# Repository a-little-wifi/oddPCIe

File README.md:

# oddPCIe
PCIe + M.2 SATA breakout for Dell Latitude laptop optical drive modular bay

The optical drive (odd) SATA ports on a number of Dell Latitude laptops from 2011-2013 have a PCIe x1 lane hidden in them, meant for use with the AE3USB01 (DP/N P5MKF) USB 3.0 expansion module:  

> 

> Optical bay port in an E6420, note the second row of pins

## Laptops featuring this port:
* E6320
* E6330 / E6430s
* E6420
* E6430
* E6440
* E6520
* E6530
* E6540 / M2800

Note: The E6440, E6540 and M2800 don't seem to support hot-plug on this PCIe port, as they never actually shipped with anything using this port (the AE3USB01's bezel doesn't even line up with the case)  

## Features:

* PCIe x1 on a USB 3.0 type-a plug compatible with common mining risers
* M.2 SATA SSD slot, since the SATA port is there anyway
* Testpoints for misc pins on the connector

> 
> 

> oddPCIe plugged in to 2 different laptops, showing the fit

> 

> 3.3V regulator power led lighting up

**This board has been manufactured and tested working**  
PCIe port only active if CLKREQ pad is connected to ground  
SATA power only active if PRES pad is connected to ground

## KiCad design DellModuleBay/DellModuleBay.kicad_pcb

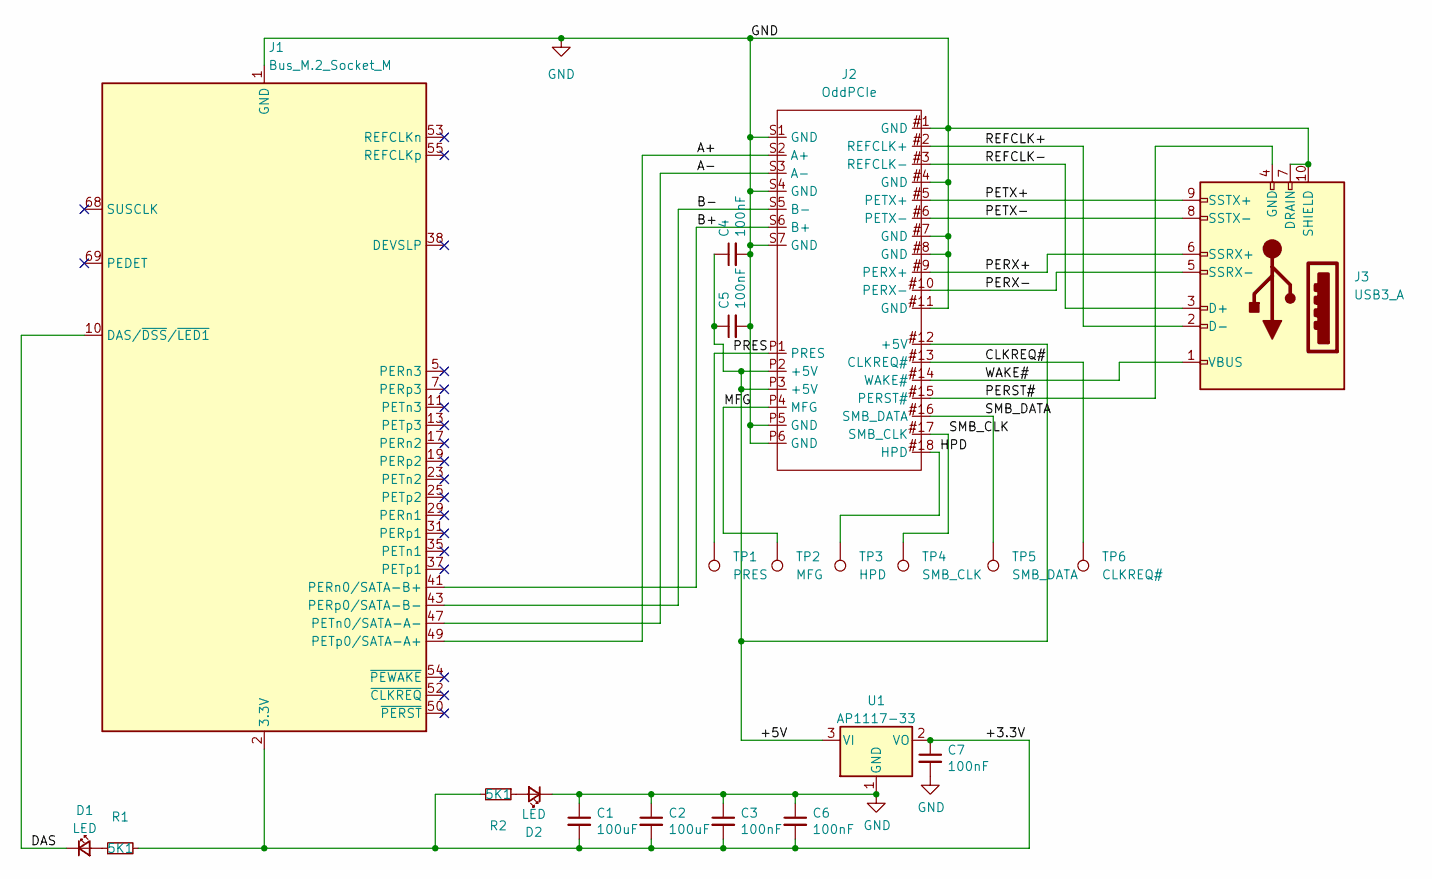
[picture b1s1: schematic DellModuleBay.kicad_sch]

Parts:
C1, C2: 100uF; C_0805_2012Metric
C3, C4, C5, C6, C7: 100nF; C_0805_2012Metric
D1, D2: LED; D_0805_2012Metric
J1: Bus_M.2_Socket_M; m-key
J2: OddPCIe
J3: USB3_A; susb3
R1, R2: 5K1; R_0603_1608Metric
TP1: PRES; TestPoint_Pad_D1.5mm
TP2: MFG; TestPoint_Pad_D1.5mm
TP3: HPD; TestPoint_Pad_D1.5mm
TP4: SMB_CLK; TestPoint_Pad_D1.5mm
TP5: SMB_DATA; TestPoint_Pad_D1.5mm
TP6: CLKREQ#; TestPoint_Pad_D1.5mm
U1: AP1117-33; SOT-223-3_TabPin2

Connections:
/+3.3V: C1.2, C2.2, C3.2, C6.2, C7.1, J1.2 (3.3V), J1.4 (3.3V), J1.12 (3.3V), J1.14 (3.3V), J1.16 (3.3V), J1.18 (3.3V), J1.70 (3.3V), J1.72 (3.3V), J1.74 (3.3V), R1.2, R2.2, U1.2 (VO)
/+5V: C4.1, C5.1, J2.#12 (+5V), J2.P2 (+5V), J2.P3 (+5V), U1.3 (VI)
/A+: J1.49 (PETp0/SATA-A+), J2.S2 (A+)
/A-: J1.47 (PETn0/SATA-A-), J2.S3 (A-)
/B+: J1.41 (PERn0/SATA-B+), J2.S6 (B+)
/B-: J1.43 (PERp0/SATA-B-), J2.S5 (B-)
/CLKREQ#: J2.#13 (CLKREQ#), TP6.1
/DAS: D1.1 (K), J1.10 (DAS/~DSS/~LED1)
/HPD: J2.#18 (HPD), TP3.1
/MFG: J2.P4 (MFG), TP2.1
/PERST#: J2.#15 (PERST#), J3.4 (GND)
/PERX+: J2.#9 (PERX+), J3.6 (SSRX+)
/PERX-: J2.#10 (PERX-), J3.5 (SSRX-)
/PETX+: J2.#5 (PETX+), J3.9 (SSTX+)
/PETX-: J2.#6 (PETX-), J3.8 (SSTX-)
/PRES: J2.P1 (PRES), TP1.1
/REFCLK+: J2.#2 (REFCLK+), J3.2 (D-)
/REFCLK-: J2.#3 (REFCLK-), J3.3 (D+)
/SMB_CLK: J2.#17 (SMB_CLK), TP4.1
/SMB_DATA: J2.#16 (SMB_DATA), TP5.1
/WAKE#: J2.#14 (WAKE#), J3.1 (VBUS)
GND: C1.1, C2.1, C3.1, C4.2, C5.2, C6.1, C7.2, D2.1 (K), J1.1 (GND), J1.3 (GND), J1.9 (GND), J1.15 (GND), J1.21 (GND), J1.27 (GND), J1.33 (GND), J1.39 (GND), J1.45 (GND), J1.51 (GND), J1.57 (GND), J1.71 (GND), J1.73 (GND), J1.75 (GND), J2.#1 (GND), J2.#4 (GND), J2.#7 (GND), J2.#8 (GND), J2.#11 (GND), J2.P5 (GND), J2.P6 (GND), J2.S1 (GND), J2.S4 (GND), J2.S7 (GND), J3.7 (DRAIN), J3.10 (SHIELD), U1.1 (GND)
unnamed: D1.2 (A), R1.1
unnamed: D2.2 (A), R2.1

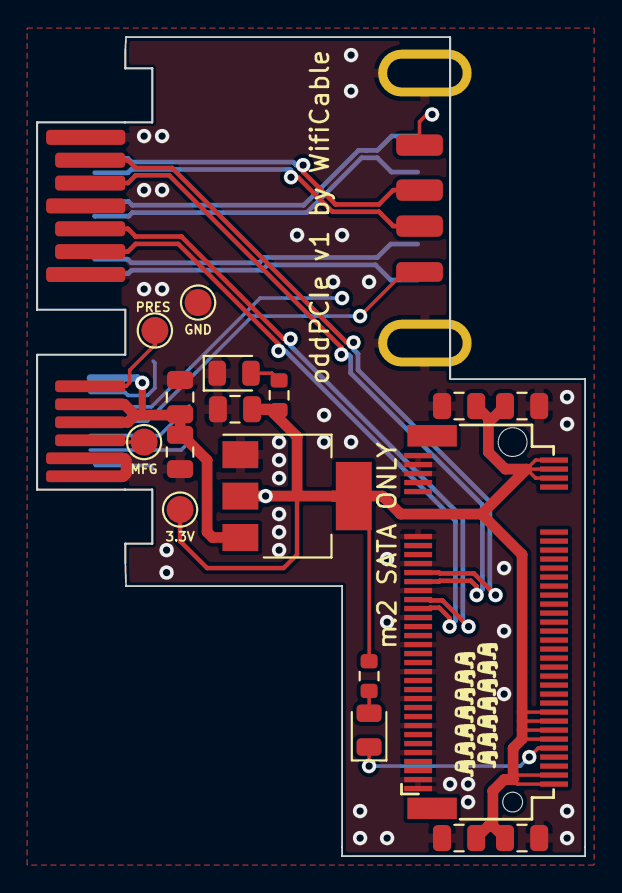
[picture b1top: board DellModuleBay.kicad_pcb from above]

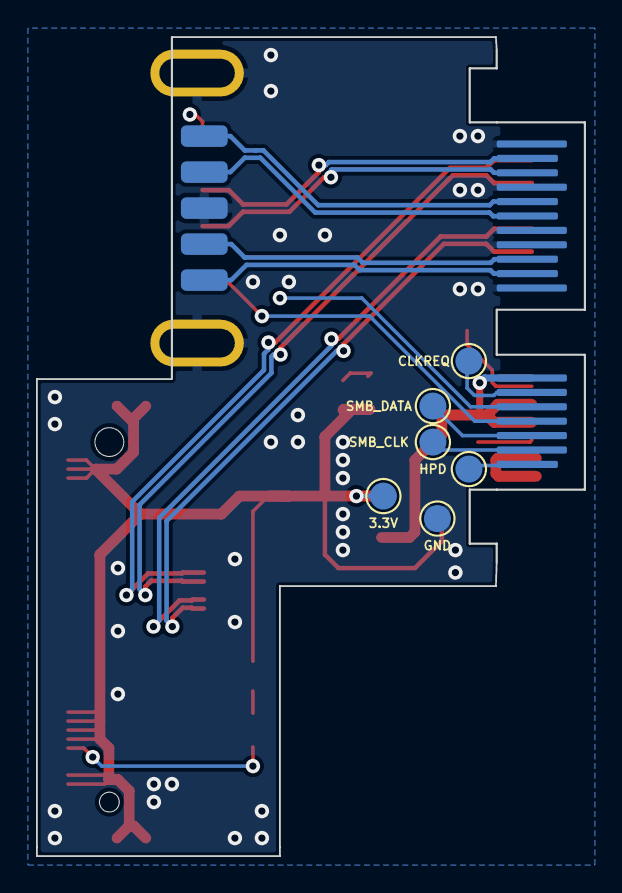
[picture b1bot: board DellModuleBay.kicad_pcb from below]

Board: 4 copper layers, 30.4 x 45.5 mm, 21 parts (4 on the bottom side), 24 nets.

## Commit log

2024-04-22 Added files and wrote readme
2025-01-13 added DP/N for USB3 module to readme
